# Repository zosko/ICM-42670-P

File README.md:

# ICM-42670-P
ICM-42670-P Module board

The ICM-42670-P is a compact 6-axis inertial measurement unit used in many modern electronic devices. It combines a 3-axis gyroscope and a 3-axis accelerometer in a single chip. This sensor is designed for applications that require motion sensing and orientation detection. It is widely used in smartphones, wearable devices, and IoT products. The sensor provides high accuracy for motion tracking and gesture recognition. It supports both I²C and SPI communication interfaces.

The ICM-42670-P is known for its low power consumption, which makes it suitable for battery-powered devices. It integrates advanced filtering features to improve the quality of sensor data. The device can detect movement, tilt, rotation, and vibration. It helps electronic systems understand their position and motion in space. The sensor is also used in robotics and drone stabilization systems. It includes programmable registers that allow developers to configure its behavior.

The sensor offers reliable performance even in small embedded systems. It can operate over a wide range of temperatures. The gyroscope in the device provides precise angular velocity measurements. The accelerometer measures linear acceleration in three directions. This sensor helps improve motion-based user interfaces in many devices. It is manufactured by TDK Corporation as part of its motion sensor products. The chip also supports embedded motion detection features that reduce the workload of the main processor. Overall, the ICM-42670-P is a reliable solution for motion-tracking applications.

## Code

Library used:
https://github.com/tdk-invn-oss/motion.arduino.ICM42670P

## Scheme

## Board

## Sponsorship

This project is kindly sponsored by [PCBWay](https://pcbway.com).
PCBWay specializes in manufacturing high-quality PCBs and makes them affordable to hobbyist and professionals alike.

The range of services they offer include PCB prototyping, assembly, instant quotes for your order, a verification process by a team
of experts and an easy to use, hassle-free order process.

I'm grateful to PCBWay for the support in creating this project.

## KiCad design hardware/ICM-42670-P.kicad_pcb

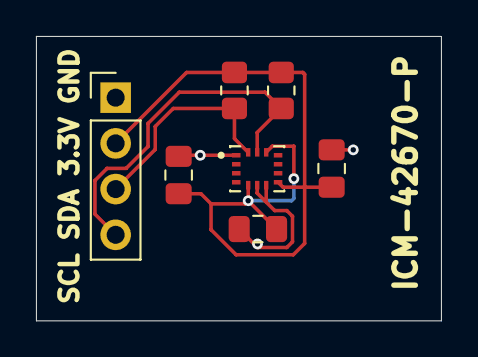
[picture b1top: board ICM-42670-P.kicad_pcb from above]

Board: 2 copper layers, 22.5 x 15.8 mm, 7 parts (0 on the bottom side), 4 nets.

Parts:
C1: 2.2uF; C_0805_2012Metric_Pad1.18x1.45mm_HandSolder
C2: 10nF; C_0805_2012Metric_Pad1.18x1.45mm_HandSolder
C3: 100nF; C_0805_2012Metric_Pad1.18x1.45mm_HandSolder
J1: Connector; PinHeader_1x04_P2.54mm_Vertical
MT1: ICM-42670-P; XDCR_ICM-42670-P
R1, R2: 10K; R_0805_2012Metric_Pad1.20x1.40mm_HandSolder

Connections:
3.3V: C1.2, C2.1, C3.2, J1.2, MT1.5 (VDDIO), MT1.8 (VDD), MT1.12 (AP_CS), R1.1, R2.1
GND: C1.1, C2.2, C3.1, J1.1, MT1.1 (AP_SDO/AP_AD0), MT1.6 (GND), MT1.7 (FSYNC)
SCL: J1.4, MT1.13 (AP_SCL/AP_SCLK), R1.2
SDA: J1.3, MT1.14 (AP_SDA/AP_SDIO/AP_SDI), R2.2

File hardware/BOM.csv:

"Reference","Value","LCSC"
"C1","2.2uF","C513763"
"C2","10nF","C49296944"
"C3","100nF","C19186128"
"J1","Connector",""
"MT1","ICM-42670-P","C3288646"
"R1,R2","10K","C84376"

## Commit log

2025-12-23 fix vias
